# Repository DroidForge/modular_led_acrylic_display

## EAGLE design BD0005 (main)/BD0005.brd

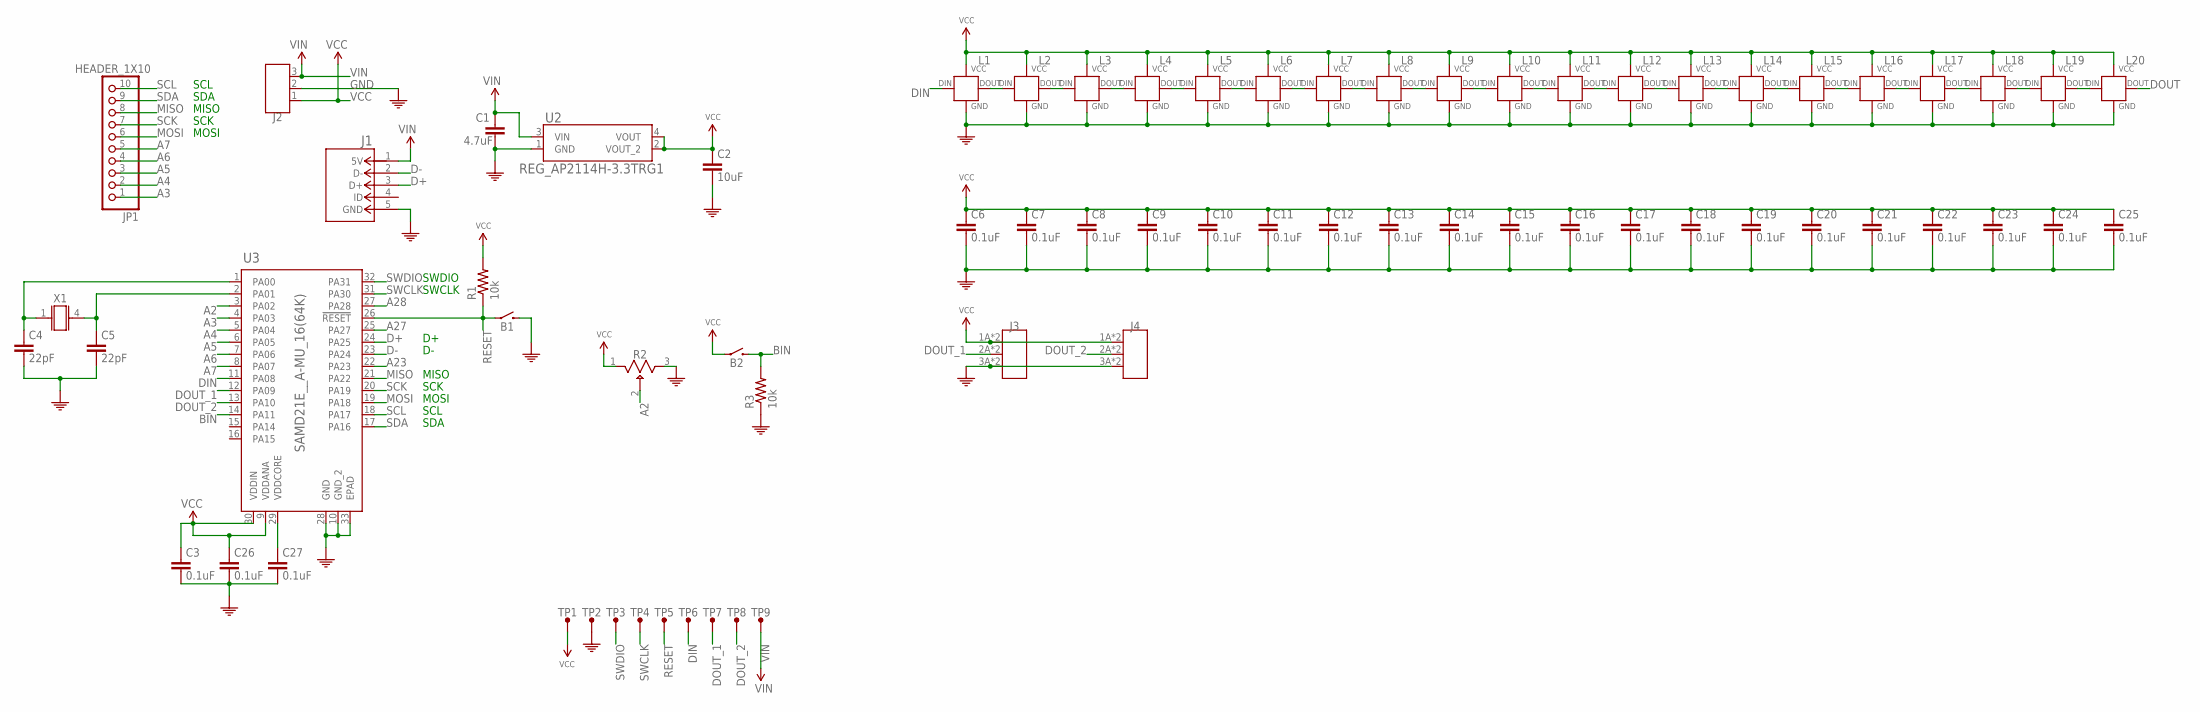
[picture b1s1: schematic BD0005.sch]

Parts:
B1, B2: SWITCH_EVQ-P7A01P; 4-SMD_BUTTON
C1: 4.7uF; 0402
C2: 10uF; 0402
C3, C6, C7, C8, C9, C10, C11, C12, C13, C14, C15, C16, C17, C18, C19, C20, C21, C22, C23, C24, C25, C26, C27: 0.1uF; 0402
C4, C5: 22pF; 0402
J1: CONN_MICROUSB_FEMALE; CON00679_5
J2: HEADER_1X3; 1X03-CLEANBIG
J3, J4: HEADER_1X3FEMALE; F3SMD_RIGHTANGLE
JP1: HEADER_1X10; 1X10-BIG
L1, L2, L3, L4, L5, L6, L7, L8, L9, L10, L11, L12, L13, L14, L15, L16, L17, L18, L19, L20: WS2812B-B; SK6812-B
R1, R3: 10k; 0402
R2: POT_THUMBWHEEL_3352T-1-104LF; THUMBWHEEL
TP1: VCC; TEST_POINT
TP2: GND; TEST_POINT
TP3: DIO; TEST_POINT
TP4: CLK; TEST_POINT
TP5: RST; TEST_POINT
TP6: DIN; TEST_POINT
TP7: DO1; TEST_POINT
TP8: DO2; TEST_POINT
TP9: VIN; TEST_POINT
U2: REG_AP2114H-3.3TRG1; SOT-223
U3: SAMD21E__A-MU_16(64K); QFN32_5X5MC_MCH
X1: XTAL_MC-146-32.7680JKA-A0:ROHS; 4-SMD_FLAT_LEADS

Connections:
A2: R2.2, U3.3 (PA02)
A3: JP1.1, U3.4 (PA03)
A4: JP1.2, U3.5 (PA04)
A5: JP1.3, U3.6 (PA05)
A6: JP1.4, U3.7 (PA06)
A7: JP1.5, U3.8 (PA07)
A23: U3.22 (PA23)
A27: U3.25 (PA27)
A28: U3.27 (PA28)
BIN: B2.2A, B2.2B, R3.P$2 (2), U3.14 (PA11)
D+: J1.3 (D+), U3.24 (PA25)
D-: J1.2 (D-), U3.23 (PA24)
DIN: L1.2 (DIN), TP6.P$1, U3.11 (PA08)
DOUT: L20.4 (DOUT)
DOUT_1: J3.2A, J3.2B, TP7.P$1, U3.12 (PA09)
DOUT_2: J4.2A, J4.2B, TP8.P$1, U3.13 (PA10)
GND: B1.2A, B1.2B, C1.P$2 (2), C2.P$2 (2), C3.P$2 (2), C4.P$2 (2), C5.P$2 (2), C6.P$2 (2), C7.P$2 (2), C8.P$2 (2), C9.P$2 (2), C10.P$2 (2), C11.P$2 (2), C12.P$2 (2), C13.P$2 (2), C14.P$2 (2), C15.P$2 (2), C16.P$2 (2), C17.P$2 (2), C18.P$2 (2), C19.P$2 (2), C20.P$2 (2), C21.P$2 (2), C22.P$2 (2), C23.P$2 (2), C24.P$2 (2), C25.P$2 (2), C26.P$2 (2), C27.P$2 (2), J1.5 (GND), J2.2, J3.3A, J3.3B, J4.3A, J4.3B, L1.1 (VSS), L2.1 (VSS), L3.1 (VSS), L4.1 (VSS), L5.1 (VSS), L6.1 (VSS), L7.1 (VSS), L8.1 (VSS), L9.1 (VSS), L10.1 (VSS), L11.1 (VSS), L12.1 (VSS), L13.1 (VSS), L14.1 (VSS), L15.1 (VSS), L16.1 (VSS), L17.1 (VSS), L18.1 (VSS), L19.1 (VSS), L20.1 (VSS), R2.3, R3.P$1 (1), TP2.P$1, U2.1 (GND), U3.10 (GND_2), U3.28 (GND), U3.33 (EPAD)
MISO: JP1.8, U3.21 (PA22)
MOSI: JP1.6, U3.19 (PA18)
unnamed: C4.P$1 (1), U3.1 (PA00), X1.1
unnamed: C5.P$1 (1), U3.2 (PA01), X1.4
unnamed: C27.P$1 (1), U3.29 (VDDCORE)
unnamed: L19.4 (DOUT), L20.2 (DIN)
unnamed: L18.4 (DOUT), L19.2 (DIN)
unnamed: L17.4 (DOUT), L18.2 (DIN)
unnamed: L16.4 (DOUT), L17.2 (DIN)
unnamed: L15.4 (DOUT), L16.2 (DIN)
unnamed: L14.4 (DOUT), L15.2 (DIN)
unnamed: L13.4 (DOUT), L14.2 (DIN)
unnamed: L12.4 (DOUT), L13.2 (DIN)
unnamed: L11.4 (DOUT), L12.2 (DIN)
unnamed: L10.4 (DOUT), L11.2 (DIN)
unnamed: L9.4 (DOUT), L10.2 (DIN)
unnamed: L8.4 (DOUT), L9.2 (DIN)
unnamed: L7.4 (DOUT), L8.2 (DIN)
unnamed: L1.4 (DOUT), L2.2 (DIN)
unnamed: L2.4 (DOUT), L3.2 (DIN)
unnamed: L3.4 (DOUT), L4.2 (DIN)
unnamed: L4.4 (DOUT), L5.2 (DIN)
unnamed: L5.4 (DOUT), L6.2 (DIN)
unnamed: L6.4 (DOUT), L7.2 (DIN)
RESET: B1.1A, B1.1B, R1.P$1 (1), TP5.P$1, U3.26 (!RESET)
SCK: JP1.7, U3.20 (PA19)
SCL: JP1.10, U3.18 (PA17)
SDA: JP1.9, U3.17 (PA16)
SWCLK: TP4.P$1, U3.31 (PA30)
SWDIO: TP3.P$1, U3.32 (PA31)
VCC: B2.1A, B2.1B, C2.P$1 (1), C3.P$1 (1), C6.P$1 (1), C7.P$1 (1), C8.P$1 (1), C9.P$1 (1), C10.P$1 (1), C11.P$1 (1), C12.P$1 (1), C13.P$1 (1), C14.P$1 (1), C15.P$1 (1), C16.P$1 (1), C17.P$1 (1), C18.P$1 (1), C19.P$1 (1), C20.P$1 (1), C21.P$1 (1), C22.P$1 (1), C23.P$1 (1), C24.P$1 (1), C25.P$1 (1), C26.P$1 (1), J2.1, J3.1A, J3.1B, J4.1A, J4.1B, L1.3 (VDD), L2.3 (VDD), L3.3 (VDD), L4.3 (VDD), L5.3 (VDD), L6.3 (VDD), L7.3 (VDD), L8.3 (VDD), L9.3 (VDD), L10.3 (VDD), L11.3 (VDD), L12.3 (VDD), L13.3 (VDD), L14.3 (VDD), L15.3 (VDD), L16.3 (VDD), L17.3 (VDD), L18.3 (VDD), L19.3 (VDD), L20.3 (VDD), R1.P$2 (2), R2.1, TP1.P$1, U2.2 (VOUT_2), U2.4 (VOUT), U3.9 (VDDANA), U3.30 (VDDIN)
VIN: C1.P$1 (1), J1.1 (5V), J2.3, TP9.P$1, U2.3 (VIN)

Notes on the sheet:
SCL
SDA
MISO
SCK
MOSI
SWCLK
SWDIO

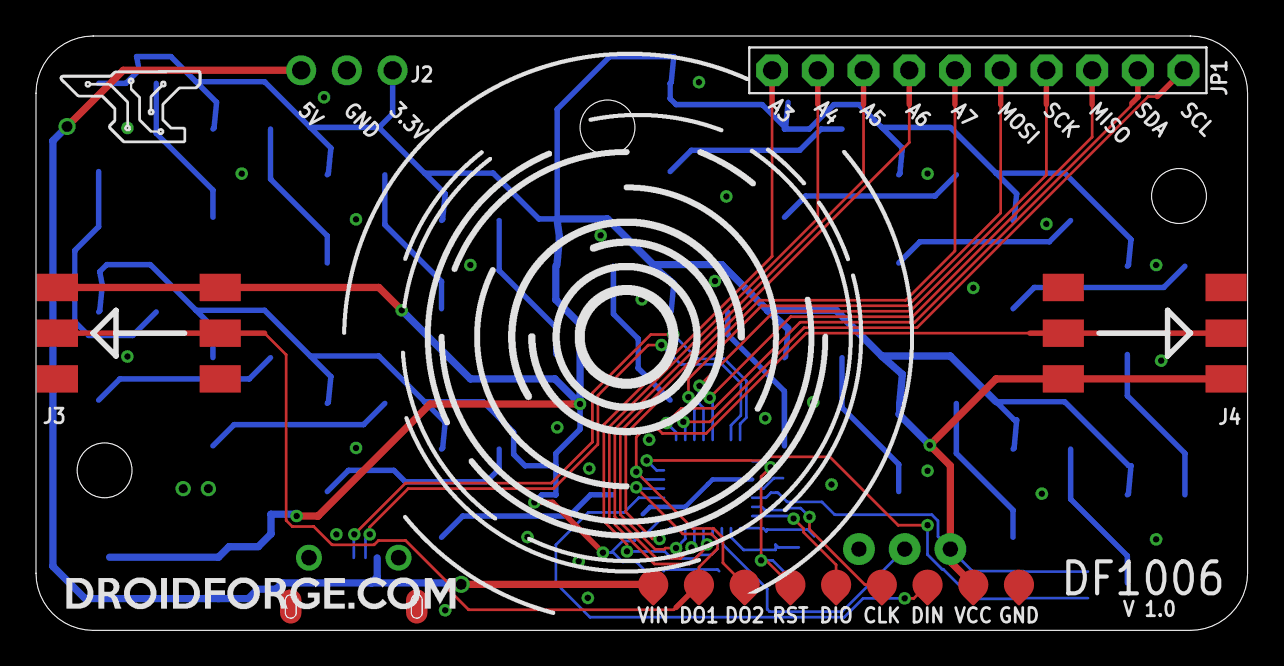
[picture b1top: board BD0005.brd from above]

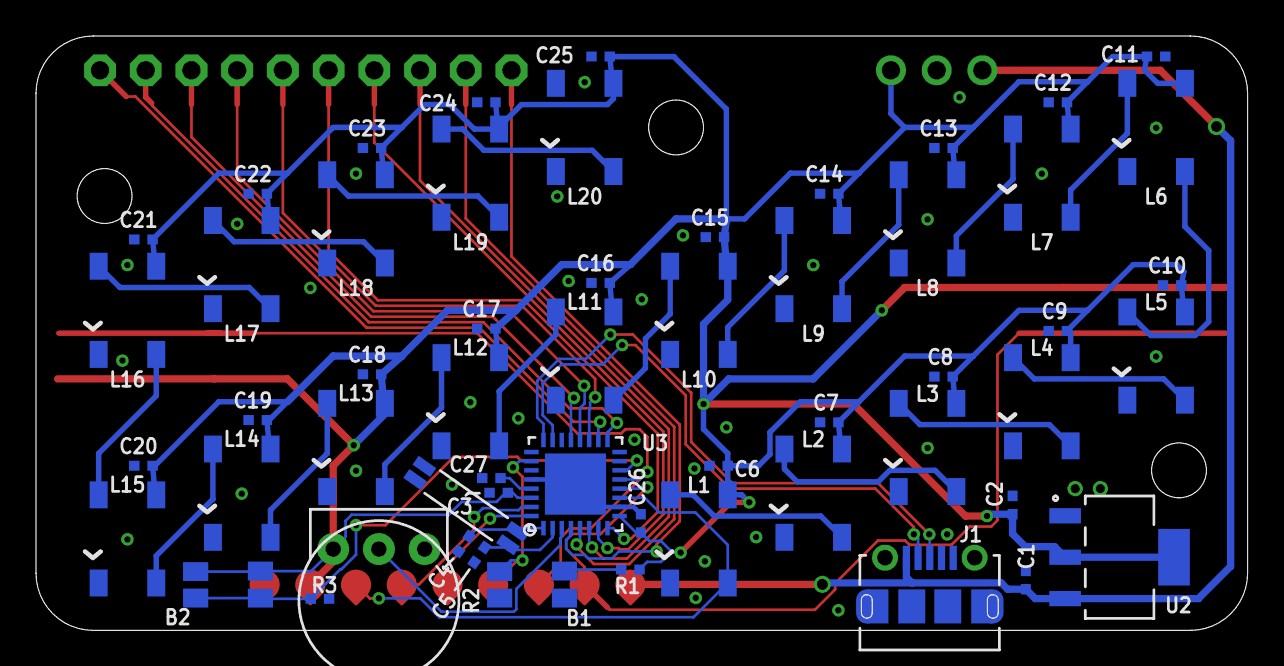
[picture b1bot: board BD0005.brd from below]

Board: 2 copper layers, 67.3 x 33.0 mm, 69 parts (56 on the bottom side), 45 nets.

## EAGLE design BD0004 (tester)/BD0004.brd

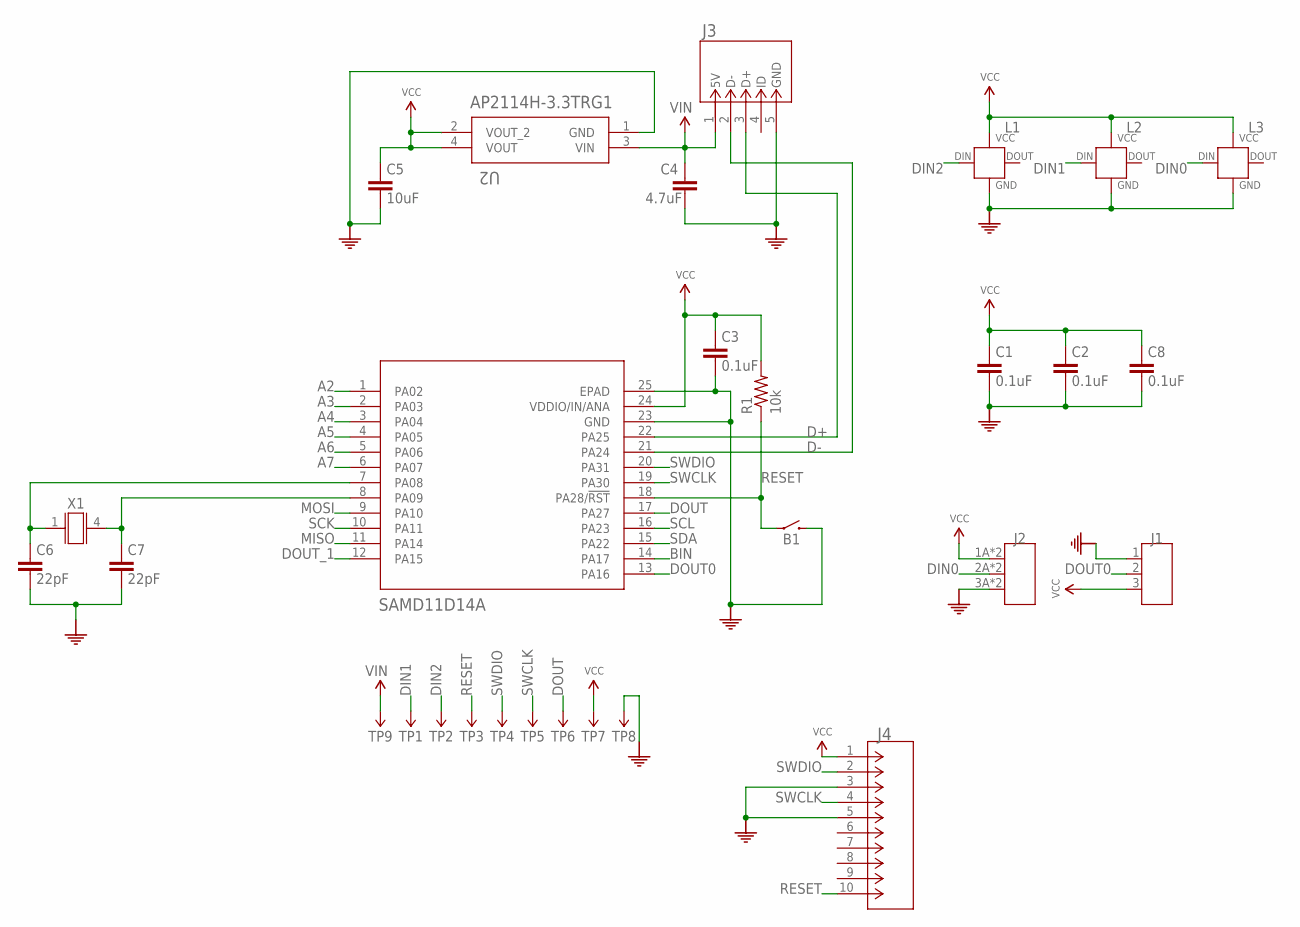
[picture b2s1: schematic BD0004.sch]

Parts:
B1: EVQ-P7A01P; 4-SMD_BUTTON
C1, C2, C3, C8: 0.1uF; 0402
C4: 4.7uF; 0402
C5: 10uF; 0402
C6, C7: 22pF; 0402
J1: HEADER_1X3MALE; M3SMD_RIGHTANGLE
J2: HEADER_1X3FEMALE; F3SMD_RIGHTANGLE
J3: CONN_MICROUSB_FEMALE; CON00679_5
J4: CORTEX-M_DEBUG_HEADER; CONN_00010C4LF
L1, L2, L3: WS2812B-B; SK6812-B
R1: 10k; 0402
TP1, TP2, TP3, TP4, TP5, TP6, TP7, TP8, TP9: POGO; R-1-CR
U1: SAMD11D14A; QFN24_4X4MC
U2: AP2114H-3.3TRG1; SOT-223
X1: MC-146-32.7680JKA-A0:ROHS; 4-SMD_FLAT_LEADS

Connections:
A2: U1.1 (PA02)
A3: U1.2 (PA03)
A4: U1.3 (PA04)
A5: U1.4 (PA05)
A6: U1.5 (PA06)
A7: U1.6 (PA07)
BIN: U1.14 (PA17)
D+: J3.3 (D+), U1.22 (PA25)
D-: J3.2 (D-), U1.21 (PA24)
DIN0: J2.2A, J2.2B, L3.2 (DIN)
DIN1: L2.2 (DIN), TP1.P$1
DIN2: L1.2 (DIN), TP2.P$1
DOUT: TP6.P$1, U1.17 (PA27)
DOUT0: J1.2, U1.13 (PA16)
DOUT_1: U1.12 (PA15)
GND: B1.2A, B1.2B, C1.P$2 (2), C2.P$2 (2), C3.P$2 (2), C4.P$2 (2), C5.P$2 (2), C6.P$2 (2), C7.P$2 (2), C8.P$2 (2), J1.1, J2.3A, J2.3B, J3.5 (GND), J4.3, J4.5, L1.1 (VSS), L2.1 (VSS), L3.1 (VSS), TP8.P$1, U1.23 (GND), U1.25 (EPAD), U2.1 (GND)
MISO: U1.11 (PA14)
MOSI: U1.9 (PA10)
unnamed: C6.P$1 (1), U1.7 (PA08), X1.1
unnamed: C7.P$1 (1), U1.8 (PA09), X1.4
RESET: B1.1A, B1.1B, J4.10, R1.P$1 (1), TP3.P$1, U1.18 (PA28/!RST)
SCK: U1.10 (PA11)
SCL: U1.16 (PA23)
SDA: U1.15 (PA22)
SWCLK: J4.4, TP5.P$1, U1.19 (PA30)
SWDIO: J4.2, TP4.P$1, U1.20 (PA31)
VCC: C1.P$1 (1), C2.P$1 (1), C3.P$1 (1), C5.P$1 (1), C8.P$1 (1), J1.3, J2.1A, J2.1B, J4.1, L1.3 (VDD), L2.3 (VDD), L3.3 (VDD), R1.P$2 (2), TP7.P$1, U1.24 (VDDIO/IN/ANA), U2.2 (VOUT_2), U2.4 (VOUT)
VIN: C4.P$1 (1), J3.1 (5V), TP9.P$1, U2.3 (VIN)

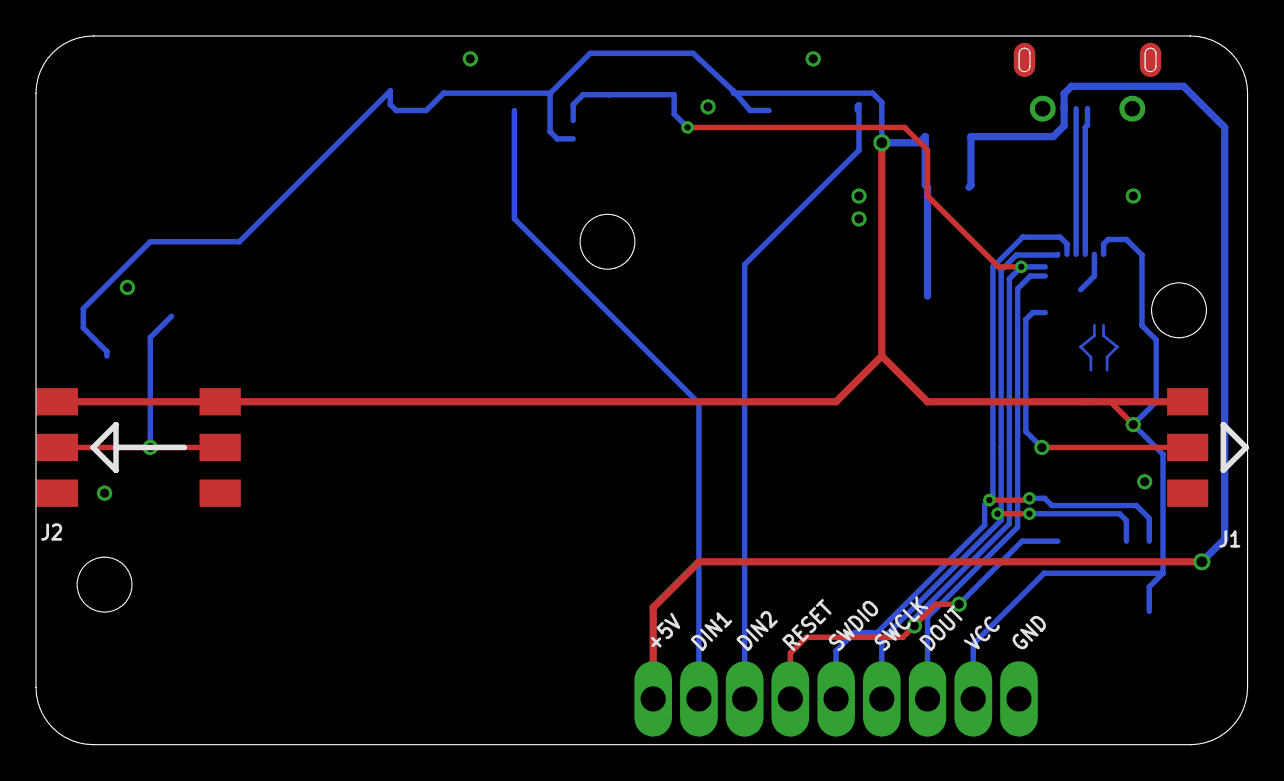
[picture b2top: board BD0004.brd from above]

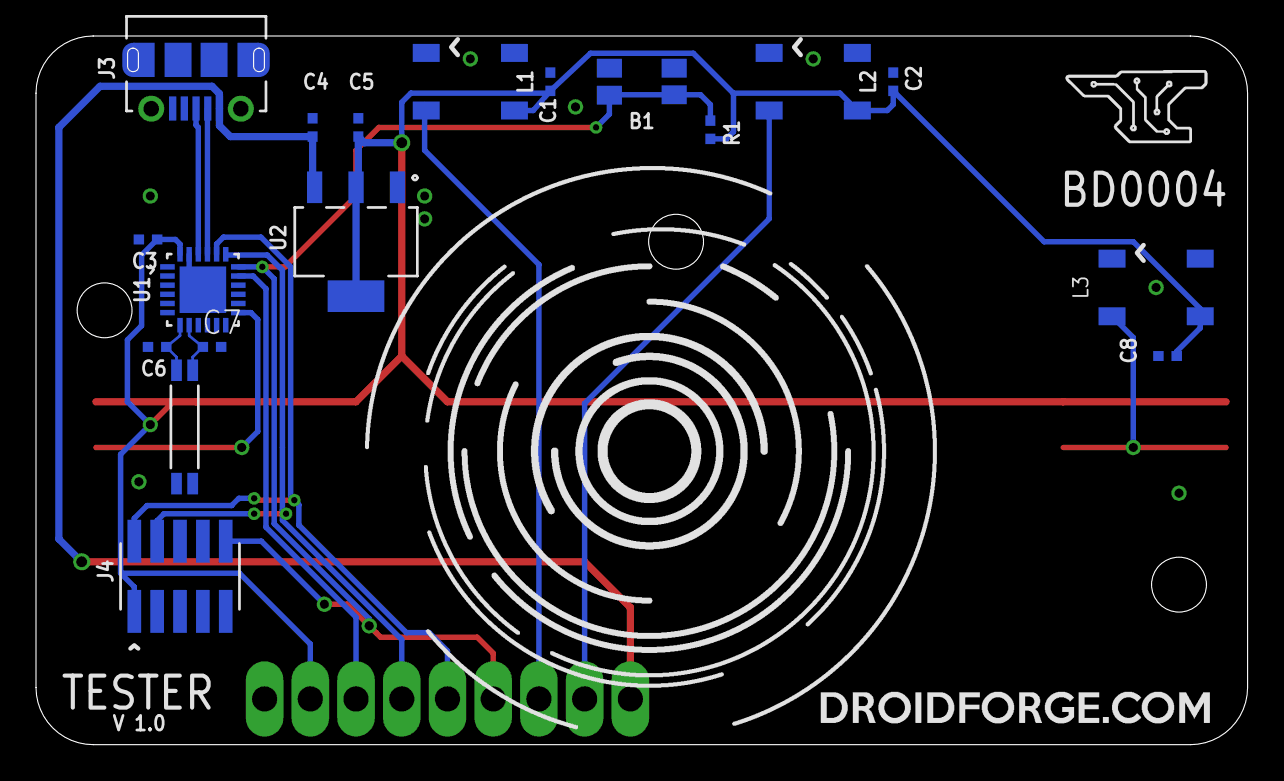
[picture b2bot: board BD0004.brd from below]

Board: 2 copper layers, 67.3 x 39.4 mm, 29 parts (18 on the bottom side), 15 nets.

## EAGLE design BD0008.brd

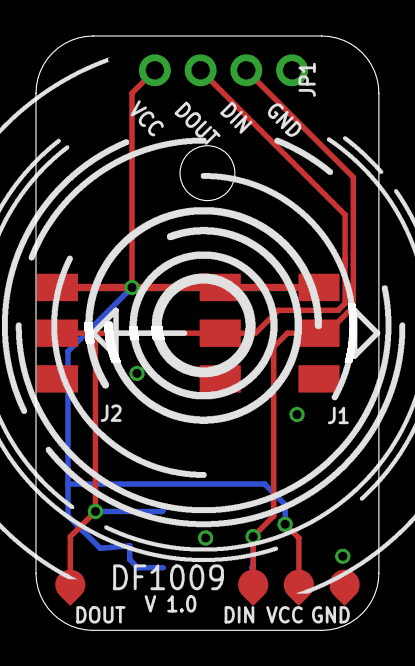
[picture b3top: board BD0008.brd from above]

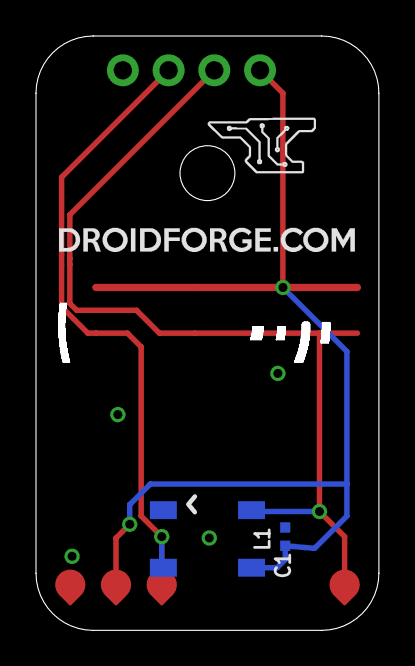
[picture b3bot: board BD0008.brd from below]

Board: 2 copper layers, 19.1 x 33.0 mm, 9 parts (2 on the bottom side), 4 nets.

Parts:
C1: 0.1uF; 0402
J1: HEADER_1X3MALE; M3SMD_RIGHTANGLE
J2: HEADER_1X3FEMALE; F3SMD_RIGHTANGLE
JP1: HEADER_1X4; 1X04-CLEANBIG
L1: WS2812B-B; SK6812-B
TP1: VCC; TEST_POINT
TP2: GND; TEST_POINT
TP3: DOUT; TEST_POINT
TP4: DIN; TEST_POINT

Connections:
DIN: J1.2, JP1.2, L1.2, TP4.P$1
DOUT: J2.2A, J2.2B, JP1.3, L1.4, TP3.P$1
GND: C1.P$2, J1.1, J2.3A, J2.3B, JP1.1, L1.1, TP2.P$1
VCC: C1.P$1, J1.3, J2.1A, J2.1B, JP1.4, L1.3, TP1.P$1

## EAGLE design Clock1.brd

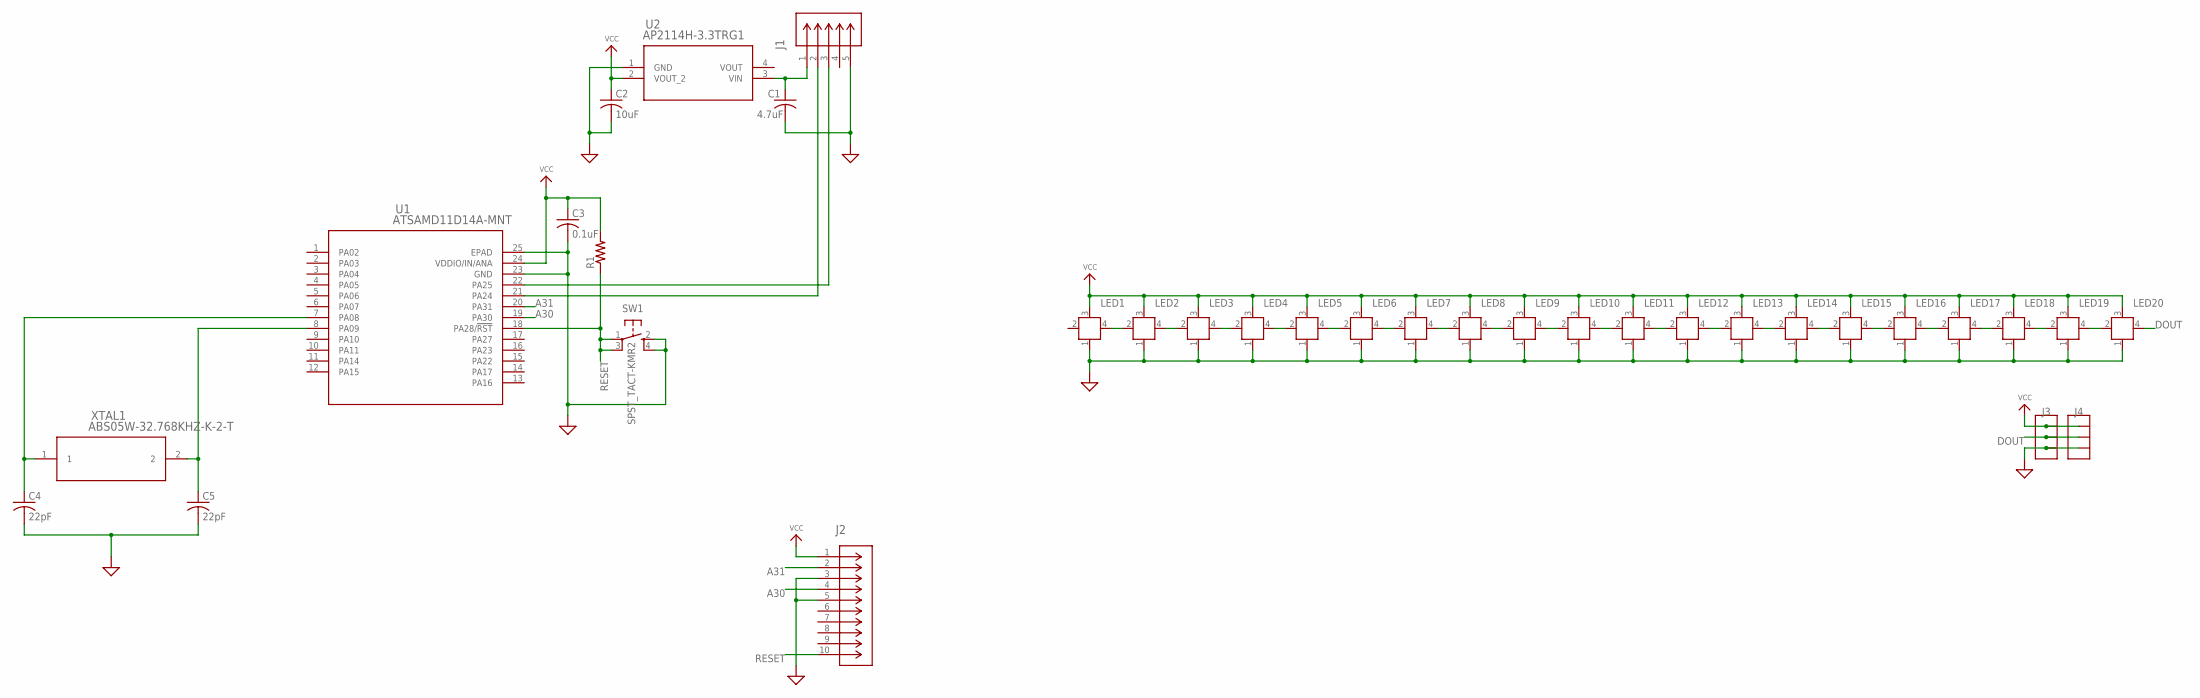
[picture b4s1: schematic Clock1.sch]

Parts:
C1: 4.7uF; C0805
C2: 10uF; C0805
C3: 0.1uF; C0402
C4, C5: 22pF; C0402
J1: 1050171001; CON00679_5
J2: 20021121-00010C4LF; CONN_00010C4LF
J3, J4: HEADER_1X3FEMALE; F3SMD
LED1, LED2, LED3, LED4, LED5, LED6, LED7, LED8, LED9, LED10, LED11, LED12, LED13, LED14, LED15, LED16, LED17, LED18, LED19, LED20: WS2812B; SK6812
R1: R-US_R0402; R0402
SW1: SPST_TACT-KMR2; KMR2
U1: ATSAMD11D14A-MNT; QFN24_4X4MC
U2: AP2114H-3.3TRG1; SOT-223
XTAL1: ABS05W-32.768KHZ-K-2-T; XTAL_ABS05

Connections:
A30: J2.4, U1.19 (PA30)
A31: J2.2, U1.20 (PA31)
DOUT: J3.2A, J3.2B, J4.2A, J4.2B, LED20.4 (DOUT)
GND: C1.2, C2.2, C3.2, C4.2, C5.2, J1.5, J2.3, J2.5, J3.3A, J3.3B, J4.3A, J4.3B, LED1.1 (VSS), LED2.1 (VSS), LED3.1 (VSS), LED4.1 (VSS), LED5.1 (VSS), LED6.1 (VSS), LED7.1 (VSS), LED8.1 (VSS), LED9.1 (VSS), LED10.1 (VSS), LED11.1 (VSS), LED12.1 (VSS), LED13.1 (VSS), LED14.1 (VSS), LED15.1 (VSS), LED16.1 (VSS), LED17.1 (VSS), LED18.1 (VSS), LED19.1 (VSS), LED20.1 (VSS), SW1.2 (S), SW1.4 (S1), U1.23 (GND), U1.25 (EPAD), U2.1 (GND)
unnamed: J1.3, U1.22 (PA25)
unnamed: J1.2, U1.21 (PA24)
unnamed: C4.1, U1.7 (PA08), XTAL1.1
unnamed: C5.1, U1.8 (PA09), XTAL1.2
unnamed: LED19.4 (DOUT), LED20.2 (DIN)
unnamed: LED18.4 (DOUT), LED19.2 (DIN)
unnamed: LED17.4 (DOUT), LED18.2 (DIN)
unnamed: LED16.4 (DOUT), LED17.2 (DIN)
unnamed: LED15.4 (DOUT), LED16.2 (DIN)
unnamed: LED14.4 (DOUT), LED15.2 (DIN)
unnamed: LED13.4 (DOUT), LED14.2 (DIN)
unnamed: LED12.4 (DOUT), LED13.2 (DIN)
unnamed: LED11.4 (DOUT), LED12.2 (DIN)
unnamed: LED10.4 (DOUT), LED11.2 (DIN)
unnamed: LED9.4 (DOUT), LED10.2 (DIN)
unnamed: LED8.4 (DOUT), LED9.2 (DIN)
unnamed: LED7.4 (DOUT), LED8.2 (DIN)
unnamed: LED1.4 (DOUT), LED2.2 (DIN)
unnamed: LED2.4 (DOUT), LED3.2 (DIN)
unnamed: LED3.4 (DOUT), LED4.2 (DIN)
unnamed: LED4.4 (DOUT), LED5.2 (DIN)
unnamed: LED5.4 (DOUT), LED6.2 (DIN)
unnamed: LED6.4 (DOUT), LED7.2 (DIN)
RESET: J2.10, R1.1, SW1.1, SW1.3 (P1), U1.18 (PA28/!RST)
VCC: C2.1, C3.1, J2.1, J3.1A, J3.1B, J4.1A, J4.1B, LED1.3 (VDD), LED2.3 (VDD), LED3.3 (VDD), LED4.3 (VDD), LED5.3 (VDD), LED6.3 (VDD), LED7.3 (VDD), LED8.3 (VDD), LED9.3 (VDD), LED10.3 (VDD), LED11.3 (VDD), LED12.3 (VDD), LED13.3 (VDD), LED14.3 (VDD), LED15.3 (VDD), LED16.3 (VDD), LED17.3 (VDD), LED18.3 (VDD), LED19.3 (VDD), LED20.3 (VDD), R1.2, U1.24 (VDDIO/IN/ANA), U2.2 (VOUT_2)
VIN: C1.1, J1.1, U2.3 (VIN)

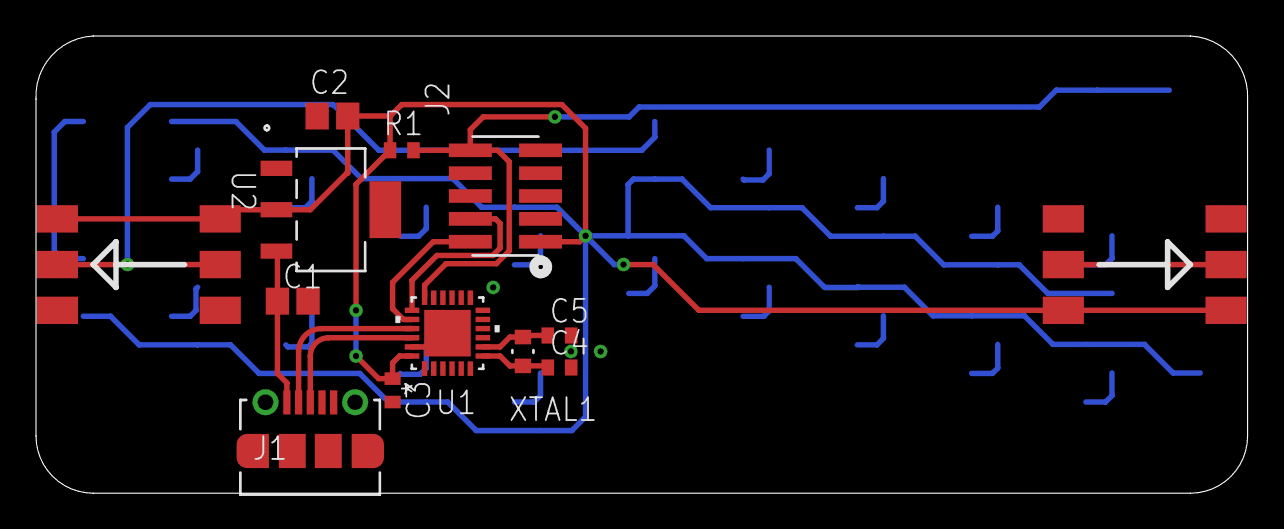
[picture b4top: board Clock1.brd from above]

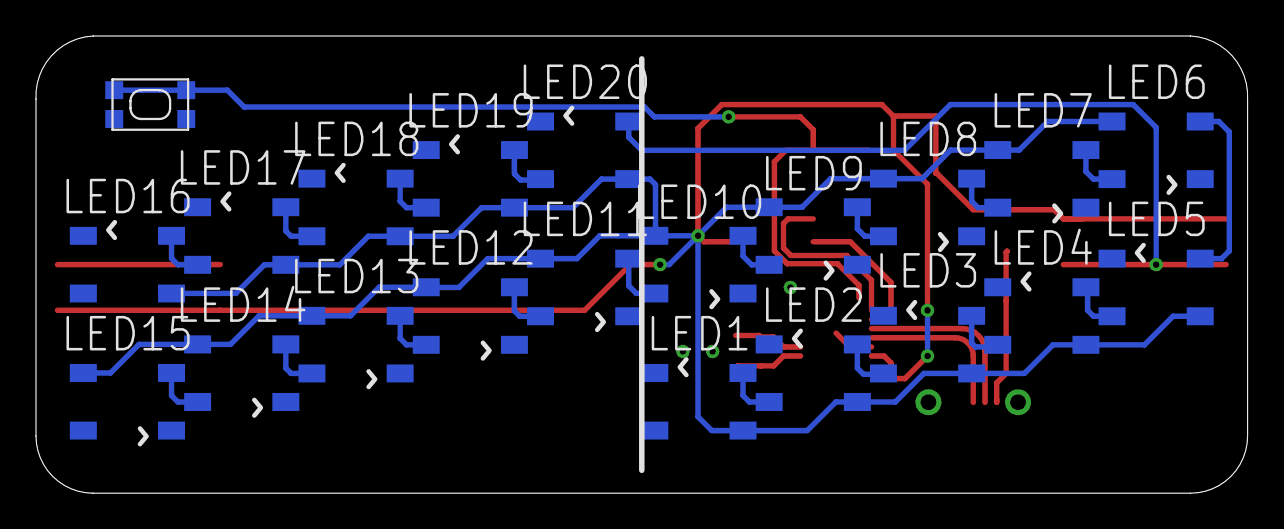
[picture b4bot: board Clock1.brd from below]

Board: 2 copper layers, 67.3 x 25.4 mm, 34 parts (21 on the bottom side), 30 nets.

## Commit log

2020-01-05 added git ignore
2020-01-05 initial release, switched git ignore files to get source tree to work
2020-01-07 Submitted and ordered from PCBways
2020-08-03 initial updates from v1. (not sure what was changed)
2020-08-03 changed SAMD11 to SAMD21E (in process)
2020-08-04 Added back in version 1 files for reference
2020-08-04 Moved and renamed files to group each board and to start tracking production revisions
2020-08-11 Placed new microcontroller on pcb
2020-08-13 Finished rerouting board for new SAMD21E processor. Also added VCC connection to processor on schematic
2020-08-17 updated microprocessor footprint and fixed silkscreen layer. Ready for review / production

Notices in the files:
parts and their libraries:
DroidForge: COPYRIGHT: Copyright (C) 2018 Accelerated Designs. All rights reserved
Clock: COPYRIGHT: Copyright (C) 2016 Accelerated Designs. All rights reserved
